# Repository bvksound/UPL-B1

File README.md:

UPL-B1 Low Distortion Generator — Functional Description (Sheets 1–5)

The UPL-B1 is a digitally controlled, ultra-low-distortion sine-wave generator. It operates by forming a precisely tuned analog feedback loop based on two integrators, a loop inverter, a fine-tuning DAC, and an ultra-slow automatic level control system. The resulting sine wave is then routed through a calibrated output attenuator to the LOW DIST output connector.

The block diagram in Sheet 1 shows how the system is organized.
What follows is the working description of each functional block in the signal path.

⸻

1. Digital Control Interface (Data Link)

(Located in sheet 1)

At the heart of the module’s control architecture is the Data Link, which acts as the communication interface between the UPL main processor and all analog functions of the generator. A chain of serial-in/parallel-out registers receives configuration words via the UPL’s internal bus. Once a word is clocked in and latched, each bit becomes a control signal for:
	•	selecting RC networks inside the frequency-defining integrators,
	•	programming the 12-bit DAC used for fine frequency tuning,
	•	configuring the ALC’s track-and-hold behavior,
	•	setting the output level via the IMD attenuator.

In this way, the Data Link provides complete, deterministic configuration of the low-distortion generator through a simple serial interface.

⸻

2. First Loop Element: Integrator 2

(Located in sheet 4)

The oscillator loop begins with Integrator 2, which receives the feedback signal from the loop inverter. This block is a precision analog integrator with a set of relay- and switch-selectable RC networks. These RC combinations determine the coarse frequency range of the oscillator.

Because the transfer function of an integrator introduces a –90° phase shift, this element contributes the first quadrature shift in the loop. The output of this block is labelled SIN. It serves as both a phase-shifted signal for the next integrator and as a key reference for amplitude monitoring in the ALC.

⸻

3. Second Loop Element: Integrator 1, and the Loop Inverter

(Both located in sheet 3)

Integrator 1 — second 90° phase shift

The SIN signal from Integrator 2 is fed into Integrator 1, which is structurally similar—another precision op-amp stage with switchable RC networks.
This second integrator produces the COS signal, shifted by another –90°.
Together, the two integrators establish the total –180° shift required by the oscillator’s feedback loop.

Fine Frequency Tuning (DAC + Summing Amplifier)

A portion of the COS signal is routed into a 12-bit DAC system, whose output feeds a summing amplifier. This mechanism provides continuous fine frequency adjustment within each coarse RC range.
The UPL’s firmware writes a digital tuning word via the Data Link, and the DAC modifies the loop dynamics subtly to achieve precise output frequency control.

Loop Inverter — completes the oscillation path

The Loop Inverter receives signals from the fine-tuning circuit and the integrator chain and produces the required additional –180° phase inversion, closing the total loop phase at 360° (0° net).
The loop inverter also establishes the oscillator’s effective feedback gain, which is later stabilized by the amplitude control system.

The output of the loop inverter is fed back to Integrator 2, completing the analog oscillator core.

⸻

4. Amplitude Regulation: The Automatic Level Control (ALC)

(Located in sheet 5)

A precision sine-wave oscillator will naturally drift or saturate unless its amplitude is regulated. In the UPL-B1, this regulation is handled by the Automatic Level Control (ALC) system.

Amplitude Sampling and Track-and-Hold

A portion of the SIN waveform is extracted and fed into a track-and-hold detector.
This allows the ALC to operate cleanly over the full frequency range of the generator—including very low frequencies—where a conventional detector would otherwise create distortion or instability.

Precision Detection and Error Generation

The sampled waveform is rectified and converted into a DC level proportional to its amplitude.
A summing amplifier compares this value to an internally established reference representing the desired output level.

Slow, Low-Distortion Control Loop

The resulting error signal passes through carefully designed low-frequency filters.
These filters ensure that the ALC’s response is extremely slow—far outside the audio band—so that no gain modulation occurs within the audible range. This is critical for achieving the exceptionally low distortion performance of the UPL-B1.

VCA Gain Element

The filtered control voltage drives a voltage-controlled amplifier (VCA) in the main signal path.
When the amplitude is too low, the VCA’s gain increases; when too high, it decreases.
When equilibrium is reached, the loop gain of the oscillator is exactly unity, resulting in a stable, clean sine of precisely controlled amplitude.

The regulated sine now moves to the final output stage.

⸻

5. Output Level Setting: IMD Attenuator

(Located in sheet 2)

The final block is the IMD Attenuator, responsible for delivering calibrated output levels to the LOW DIST connector.
The attenuator uses relay-selected resistor networks combined with precision buffer amplification. Control bits from the Data Link determine the selected attenuation step.

Unlike the ALC-governed gain element, the IMD attenuator applies fixed, accurate attenuation values that do not interact with the oscillator’s internal amplitude regulation. This ensures:
	•	repeatable, calibration-grade output levels,
	•	reliable IMD and THD measurement conditions,
	•	and isolation of the internal oscillator loop from load-dependent variations.

The output of this attenuator is the module’s LOW DIST signal.

⸻

Complete Signal Flow (at a glance)
	1.	UPL processor configures the module via the Data Link (Sheet 1).
	2.	The signal enters Integrator 2 (Sheet 4) which adds the first –90° phase shift.
	3.	It then enters Integrator 1 (Sheet 3) for another –90° shift, producing COS.
	4.	The signal passes through the fine-tuning DAC and the Loop Inverter (Sheet 3), closing the loop.
	5.	The resulting oscillation is amplitude-stabilized by the ALC system (Sheet 5).
	6.	The regulated sine enters the IMD Attenuator (Sheet 2).
	7.	The final output appears as LOW DIST, ready for measurement applications.

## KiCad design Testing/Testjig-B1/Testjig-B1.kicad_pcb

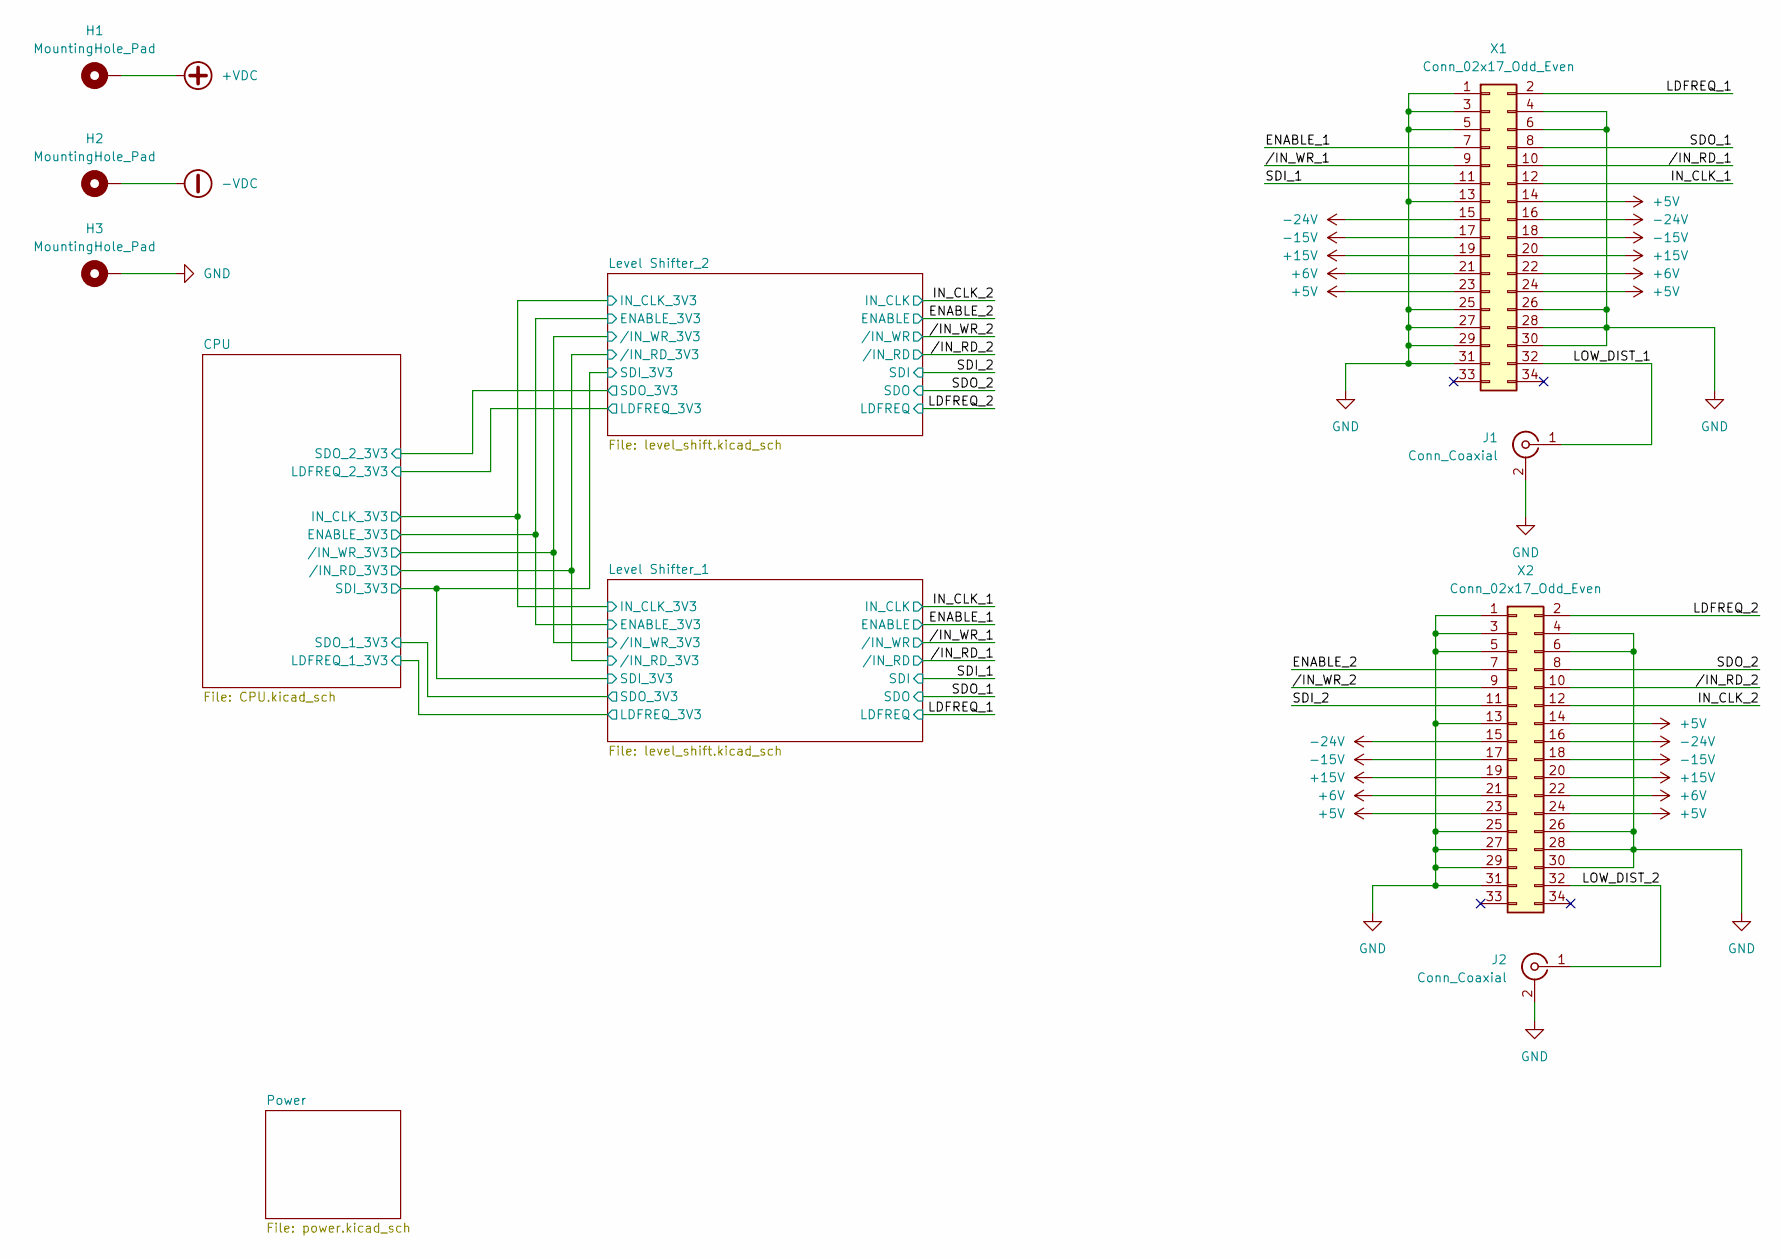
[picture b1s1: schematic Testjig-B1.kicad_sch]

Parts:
H1, H2, H3: MountingHole_Pad; MountingHole_6.4mm_M6_DIN965_Pad
J1, J2: Conn_Coaxial; BNC_Amphenol_031-5539_Vertical
X1, X2: Conn_02x17_Odd_Even; IDC-Header_2x17_P2.54mm_Vertical

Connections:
+5V: X1.14, X1.23, X1.24, X2.14, X2.23, X2.24; also elsewhere on the board
+6V: X1.21, X1.22, X2.21, X2.22; also elsewhere on the board
+15V: X1.19, X1.20, X2.19, X2.20; also elsewhere on the board
+VDC: H1.1 (1_1); also elsewhere on the board
-15V: X1.17, X1.18, X2.17, X2.18; also elsewhere on the board
-24V: X1.15, X1.16, X2.15, X2.16; also elsewhere on the board
-VDC: H2.1 (1_1); also elsewhere on the board
/ENABLE_1: X1.7; also elsewhere on the board
/ENABLE_2: X2.7; also elsewhere on the board
/IN_CLK_1: X1.12; also elsewhere on the board
/IN_CLK_2: X2.12; also elsewhere on the board
/LDFREQ_1: X1.2; also elsewhere on the board
/LDFREQ_2: X2.2; also elsewhere on the board
/LOW_DIST_1: J1.1 (In), X1.32
/LOW_DIST_2: J2.1 (In), X2.32
/SDI_1: X1.11; also elsewhere on the board
/SDI_2: X2.11; also elsewhere on the board
/SDO_1: X1.8; also elsewhere on the board
/SDO_2: X2.8; also elsewhere on the board
//IN_RD_1: X1.10; also elsewhere on the board
//IN_RD_2: X2.10; also elsewhere on the board
//IN_WR_1: X1.9; also elsewhere on the board
//IN_WR_2: X2.9; also elsewhere on the board
GND: H3.1 (1_1), J1.2 (Ext), J2.2 (Ext), X1.1, X1.3, X1.4, X1.5, X1.6, X1.13, X1.25, X1.26, X1.27, X1.28, X1.29, X1.30, X1.31, X2.1, X2.3, X2.4, X2.5, X2.6, X2.13, X2.25, X2.26, X2.27, X2.28, X2.29, X2.30, X2.31; also elsewhere on the board

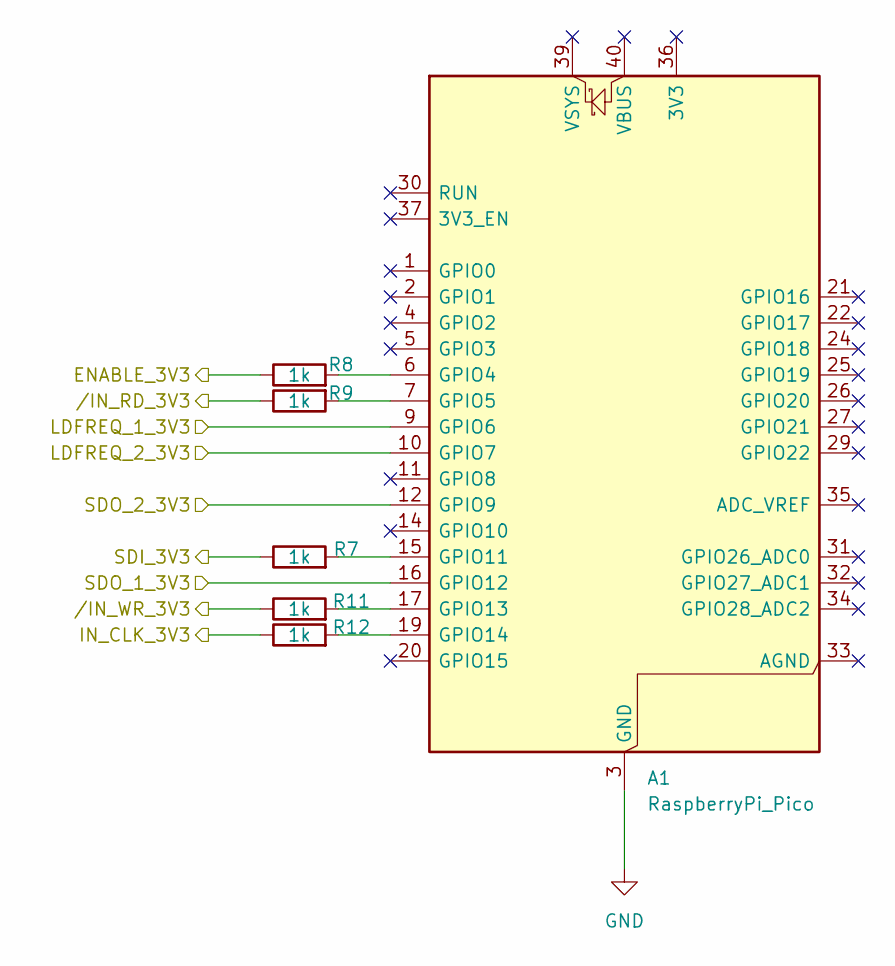
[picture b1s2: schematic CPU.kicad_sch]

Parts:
A1: RaspberryPi_Pico; RaspberryPi_Pico_Common_Unspecified
R7, R8, R9, R11, R12: 1k; R_0805_2012Metric

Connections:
/CPU/ENABLE_3V3: R8.1; also elsewhere on the board
/CPU/IN_CLK_3V3: R12.1; also elsewhere on the board
/CPU/LDFREQ_1_3V3: A1.9 (GPIO6); also elsewhere on the board
/CPU/LDFREQ_2_3V3: A1.10 (GPIO7); also elsewhere on the board
/CPU/SDI_3V3: R7.1; also elsewhere on the board
/CPU/SDO_1_3V3: A1.16 (GPIO12); also elsewhere on the board
/CPU/SDO_2_3V3: A1.12 (GPIO9); also elsewhere on the board
/CPU//IN_RD_3V3: R9.1; also elsewhere on the board
/CPU//IN_WR_3V3: R11.1; also elsewhere on the board
GND: A1.3 (GND), A1.8 (GND), A1.13 (GND), A1.18 (GND), A1.23 (GND), A1.28 (GND), A1.38 (GND); also elsewhere on the board
unnamed: A1.6 (GPIO4), R8.2
unnamed: A1.7 (GPIO5), R9.2
unnamed: A1.15 (GPIO11), R7.2
unnamed: A1.17 (GPIO13), R11.2
unnamed: A1.19 (GPIO14), R12.2

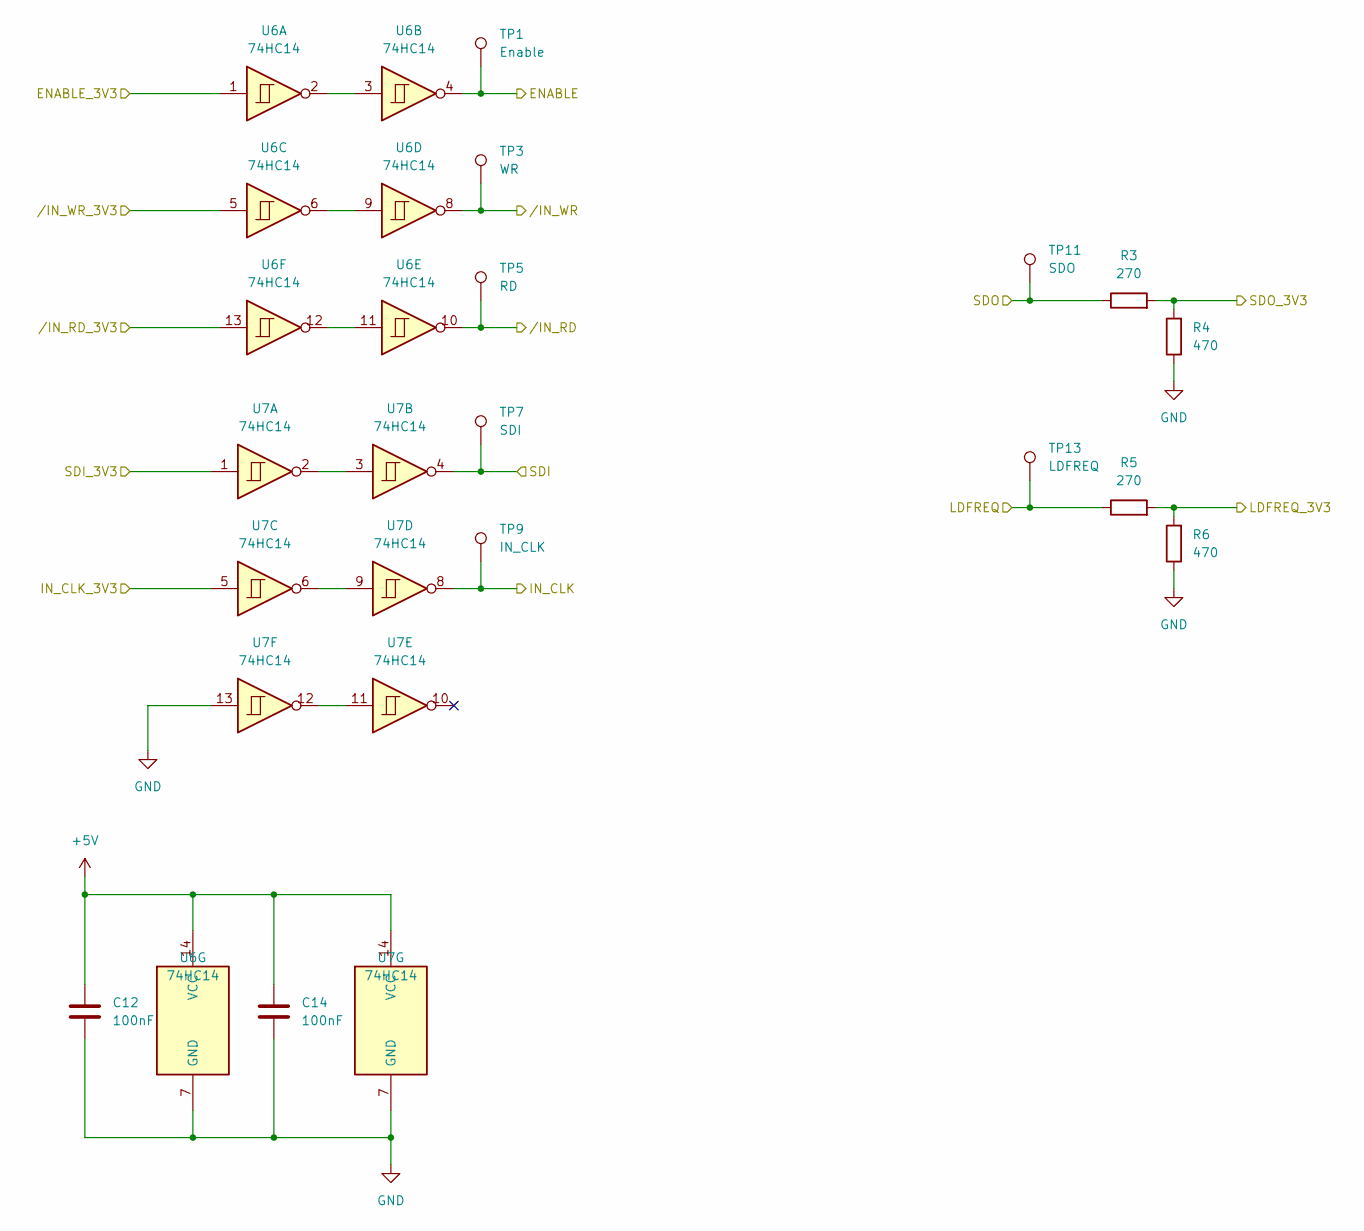
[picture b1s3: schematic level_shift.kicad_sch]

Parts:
C12, C14: 100nF; C_0805_2012Metric_Pad1.18x1.45mm_HandSolder
R3, R5: 270; R_0805_2012Metric
R4, R6: 470; R_0805_2012Metric
TP1: Enable; TestPoint_Loop_D2.60mm_Drill1.4mm_Beaded
TP3: WR; TestPoint_Loop_D2.60mm_Drill1.4mm_Beaded
TP5: RD; TestPoint_Loop_D2.60mm_Drill1.4mm_Beaded
TP7: SDI; TestPoint_Loop_D2.60mm_Drill1.4mm_Beaded
TP9: IN_CLK; TestPoint_Loop_D2.60mm_Drill1.4mm_Beaded
TP11: SDO; TestPoint_Loop_D2.60mm_Drill1.4mm_Beaded
TP13: LDFREQ; TestPoint_Loop_D2.60mm_Drill1.4mm_Beaded
U6, U7: 74HC14; SOIC-14_3.9x8.7mm_P1.27mm

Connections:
+5V: C12.1, C14.1, U6.14 (VCC), U7.14 (VCC); also elsewhere on the board
/CPU/ENABLE_3V3: U6.1; also elsewhere on the board
/CPU/IN_CLK_3V3: U7.5; also elsewhere on the board
/CPU/LDFREQ_1_3V3: R5.2, R6.2; also elsewhere on the board
/CPU/SDI_3V3: U7.1; also elsewhere on the board
/CPU/SDO_1_3V3: R3.2, R4.2; also elsewhere on the board
/CPU//IN_RD_3V3: U6.13; also elsewhere on the board
/CPU//IN_WR_3V3: U6.5; also elsewhere on the board
/ENABLE_1: TP1.1 (1_1), U6.4; also elsewhere on the board
/IN_CLK_1: TP9.1 (1_1), U7.8; also elsewhere on the board
/LDFREQ_1: R5.1, TP13.1 (1_1); also elsewhere on the board
/SDI_1: TP7.1 (1_1), U7.4; also elsewhere on the board
/SDO_1: R3.1, TP11.1 (1_1); also elsewhere on the board
//IN_RD_1: TP5.1 (1_1), U6.10; also elsewhere on the board
//IN_WR_1: TP3.1 (1_1), U6.8; also elsewhere on the board
GND: C12.2, C14.2, R4.1, R6.1, U6.7 (GND), U7.7 (GND), U7.13; also elsewhere on the board
unnamed: U6.2, U6.3
unnamed: U6.6, U6.9
unnamed: U6.11, U6.12
unnamed: U7.2, U7.3
unnamed: U7.6, U7.9
unnamed: U7.11, U7.12

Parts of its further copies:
C13, C15: 100nF; C_0805_2012Metric_Pad1.18x1.45mm_HandSolder
R13, R14: 270; R_0805_2012Metric
R15, R16: 470; R_0805_2012Metric
TP2: Enable; TestPoint_Loop_D2.60mm_Drill1.4mm_Beaded
TP4: WR; TestPoint_Loop_D2.60mm_Drill1.4mm_Beaded
TP6: RD; TestPoint_Loop_D2.60mm_Drill1.4mm_Beaded
TP8: SDI; TestPoint_Loop_D2.60mm_Drill1.4mm_Beaded
TP10: IN_CLK; TestPoint_Loop_D2.60mm_Drill1.4mm_Beaded
TP12: SDO; TestPoint_Loop_D2.60mm_Drill1.4mm_Beaded
TP14: LDFREQ; TestPoint_Loop_D2.60mm_Drill1.4mm_Beaded
U8, U9: 74HC14; SOIC-14_3.9x8.7mm_P1.27mm

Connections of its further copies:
+5V: C13.1, C15.1, U8.14 (VCC), U9.14 (VCC); also elsewhere on the board
/CPU/ENABLE_3V3: U8.1; also elsewhere on the board
/CPU/IN_CLK_3V3: U9.5; also elsewhere on the board
/CPU/LDFREQ_2_3V3: R14.2, R16.2; also elsewhere on the board
/CPU/SDI_3V3: U9.1; also elsewhere on the board
/CPU/SDO_2_3V3: R13.2, R15.2; also elsewhere on the board
/CPU//IN_RD_3V3: U8.13; also elsewhere on the board
/CPU//IN_WR_3V3: U8.5; also elsewhere on the board
/ENABLE_2: TP2.1 (1_1), U8.4; also elsewhere on the board
/IN_CLK_2: TP10.1 (1_1), U9.8; also elsewhere on the board
/LDFREQ_2: R14.1, TP14.1 (1_1); also elsewhere on the board
/SDI_2: TP8.1 (1_1), U9.4; also elsewhere on the board
/SDO_2: R13.1, TP12.1 (1_1); also elsewhere on the board
//IN_RD_2: TP6.1 (1_1), U8.10; also elsewhere on the board
//IN_WR_2: TP4.1 (1_1), U8.8; also elsewhere on the board
GND: C13.2, C15.2, R15.1, R16.1, U8.7 (GND), U9.7 (GND), U9.13; also elsewhere on the board
unnamed: U8.2, U8.3
unnamed: U8.6, U8.9
unnamed: U8.11, U8.12
unnamed: U9.2, U9.3
unnamed: U9.6, U9.9
unnamed: U9.11, U9.12

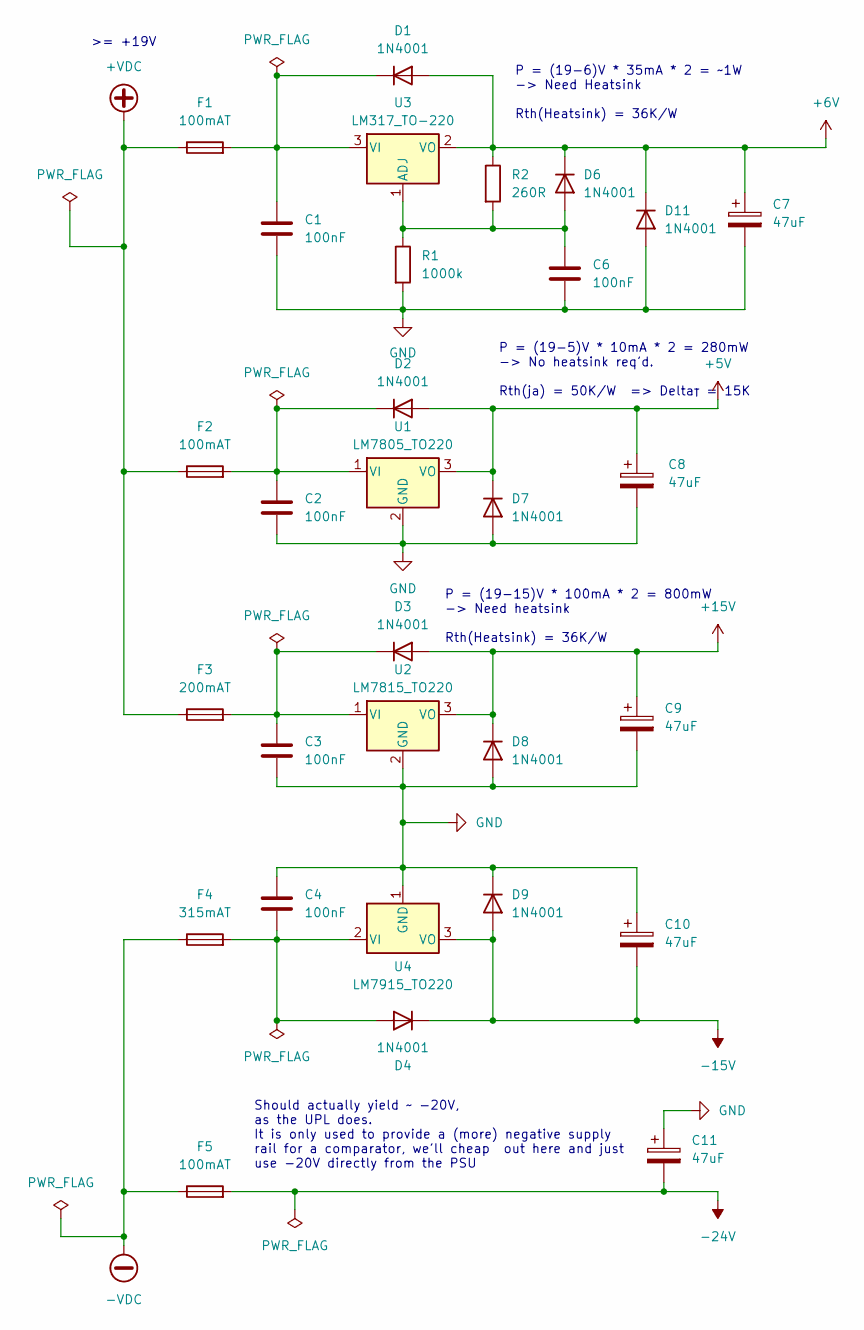
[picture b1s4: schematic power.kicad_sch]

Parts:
C1, C2, C3, C4, C6: 100nF; C_0805_2012Metric_Pad1.18x1.45mm_HandSolder
C7, C8, C9, C10, C11: 47uF; CP_Radial_D6.3mm_P2.50mm
D1, D2, D3, D4, D6, D7, D8, D9, D11: 1N4001; D_DO-41_SOD81_P10.16mm_Horizontal
F1, F2, F5: 100mAT; Fuseholder_Cylinder-5x20mm_Schurter_0031_8201_Horizontal_Op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
F3: 200mAT; Fuseholder_Cylinder-5x20mm_Schurter_0031_8201_Horizontal_Op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
F4: 315mAT; Fuseholder_Cylinder-5x20mm_Schurter_0031_8201_Horizontal_Op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
R1: 1000k; R_0805_2012Metric
R2: 260R; R_0805_2012Metric
U1: LM7805_TO220; TO-220-3_Vertical
U2: LM7815_TO220; TO-220-3_Vertical
U3: LM317_TO-220; TO-220-3_Vertical
U4: LM7915_TO220; TO-220-3_Vertical

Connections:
+5V: C8.1, D2.2 (A), D7.1 (K), U1.3 (VO); also elsewhere on the board
+6V: C7.1, D1.2 (A), D6.1 (K), D11.1 (K), R2.1, U3.2 (VO); also elsewhere on the board
+15V: C9.1, D3.2 (A), D8.1 (K), U2.3 (VO); also elsewhere on the board
+VDC: F1.1, F2.1, F3.1; also elsewhere on the board
-15V: C10.2, D4.1 (K), D9.2 (A), U4.3 (VO); also elsewhere on the board
-24V: C11.2, F5.2; also elsewhere on the board
-VDC: F4.1, F5.1; also elsewhere on the board
GND: C1.2, C2.2, C3.2, C4.1, C6.2, C7.2, C8.2, C9.2, C10.1, C11.1, D7.2 (A), D8.2 (A), D9.1 (K), D11.2 (A), R1.2, U1.2 (GND), U2.2 (GND), U4.1 (GND); also elsewhere on the board
unnamed: C1.1, D1.1 (K), F1.2, U3.3 (VI)
unnamed: C2.1, D2.1 (K), F2.2, U1.1 (VI)
unnamed: C3.1, D3.1 (K), F3.2, U2.1 (VI)
unnamed: C4.2, D4.2 (A), F4.2, U4.2 (VI)
unnamed: C6.1, D6.2 (A), R1.1, R2.2, U3.1 (ADJ)

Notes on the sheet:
>= +19V
P = (19-15)V * 100mA * 2 = 800mW -> Need heatsink Rth(Heatsink) = 36K/W
Should actually yield ~ -20V, as the UPL does. It is only used to provide a (more) negative supply rail for a comparator, we'll cheap out here and just use -20V directly from the PSU
P = (19-6)V * 35mA * 2 = ~1W -> Need Heatsink Rth(Heatsink) = 36K/W
P = (19-5)V * 10mA * 2 = 280mW -> No heatsink req'd. Rth(ja) = 50K/W => Delta_{T} = 15K

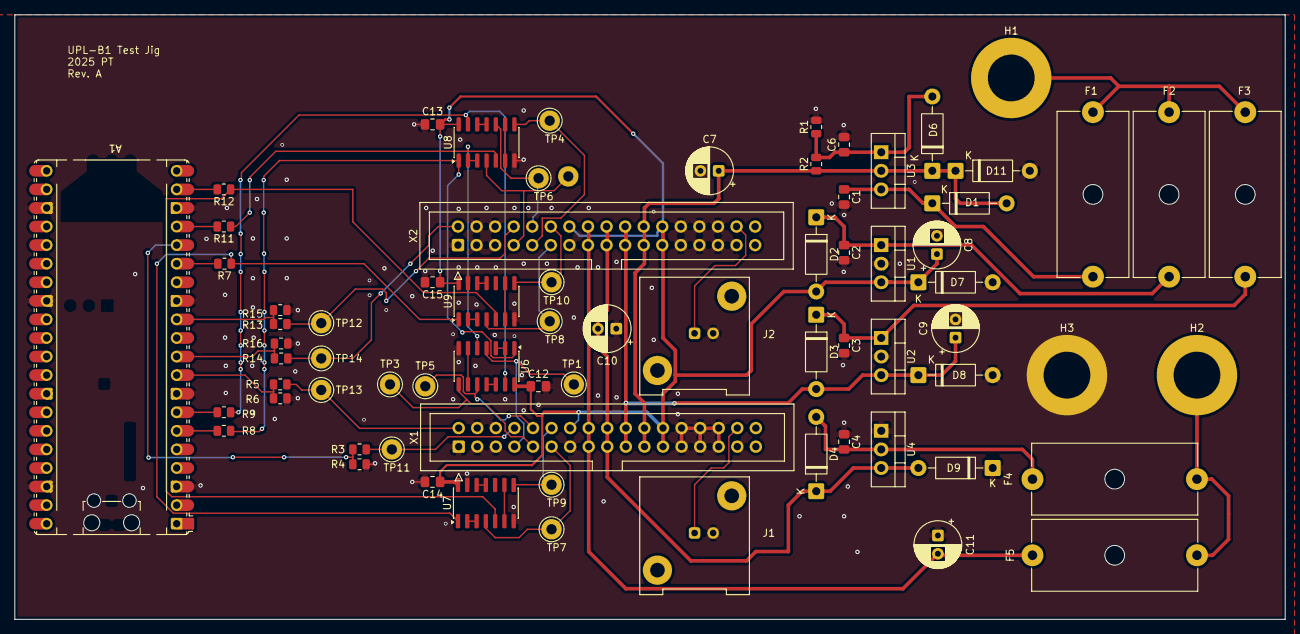
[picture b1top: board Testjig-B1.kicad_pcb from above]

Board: 2 copper layers, 173.7 x 82.7 mm, 73 parts (1 on the bottom side), 55 nets.

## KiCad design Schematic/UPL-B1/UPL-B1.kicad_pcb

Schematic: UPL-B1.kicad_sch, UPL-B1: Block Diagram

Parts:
X1: 5102159-8; CONN_5103311-7_TYC; Mouser Part Number 571-5102159-8
X3, X4: Conn_01x06_Pin; PinHeader_1x06_P2.54mm_Vertical

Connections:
+5V: X1.23, X1.24, X4.1; also elsewhere on the board
+6V: X1.21, X1.22, X4.5
+15V: X1.19, X1.20, X4.2; also elsewhere on the board
-5V: X1.14
-15V: X1.17, X1.18, X4.3; also elsewhere on the board
-24V: X1.15, X1.16, X4.4; also elsewhere on the board
/CLK: X3.4; also elsewhere on the board
/ENABLE: X1.7, X4.6; also elsewhere on the board
/IN_CLK: X1.12; also elsewhere on the board
/LDFREQ: X1.2
/LOW_DIST: X1.34; also elsewhere on the board
/SDI: X1.11, X3.5; also elsewhere on the board
/SDO: X1.8, X3.6; also elsewhere on the board
/WR: X3.1; also elsewhere on the board
//IN_RD: X1.10; also elsewhere on the board
//IN_WR: X1.9; also elsewhere on the board
/~RD: X3.3; also elsewhere on the board
/~WR: X3.2; also elsewhere on the board
GNDD: X1.1, X1.3, X1.4, X1.5, X1.6, X1.13, X1.25, X1.26, X1.27, X1.28, X1.29, X1.30, X1.31, X1.32, X1.33; also elsewhere on the board

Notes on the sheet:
2/3/4/5
T & H (Track & Hold == Sample & Hold) CONTROL
SUMMIERVERSTÄRKER
D31
-6V2
FREQ TUNE
IMD ATTEN
INTEGRATOR 1
D22,N20
D22
D32, N35
12bit
REGLER STABILIZER
D51 N56
N52
D32
SHEET
V500
N51
Integrator 2
V505..V508
V504 C504 N53
D50
COS
N401
X1A 16
N54 V512
SUMMIERVERSTÄRKER SUMMING AMPLIFIER
10Hz ... 110kHz
D23
2/3/4
V510 C551 N55
D30
SUMMING AMPLIFIFER
~ 2V7_{EFF}
V=0..-20dB
+ -
N301
D21
LOOP INVERTER

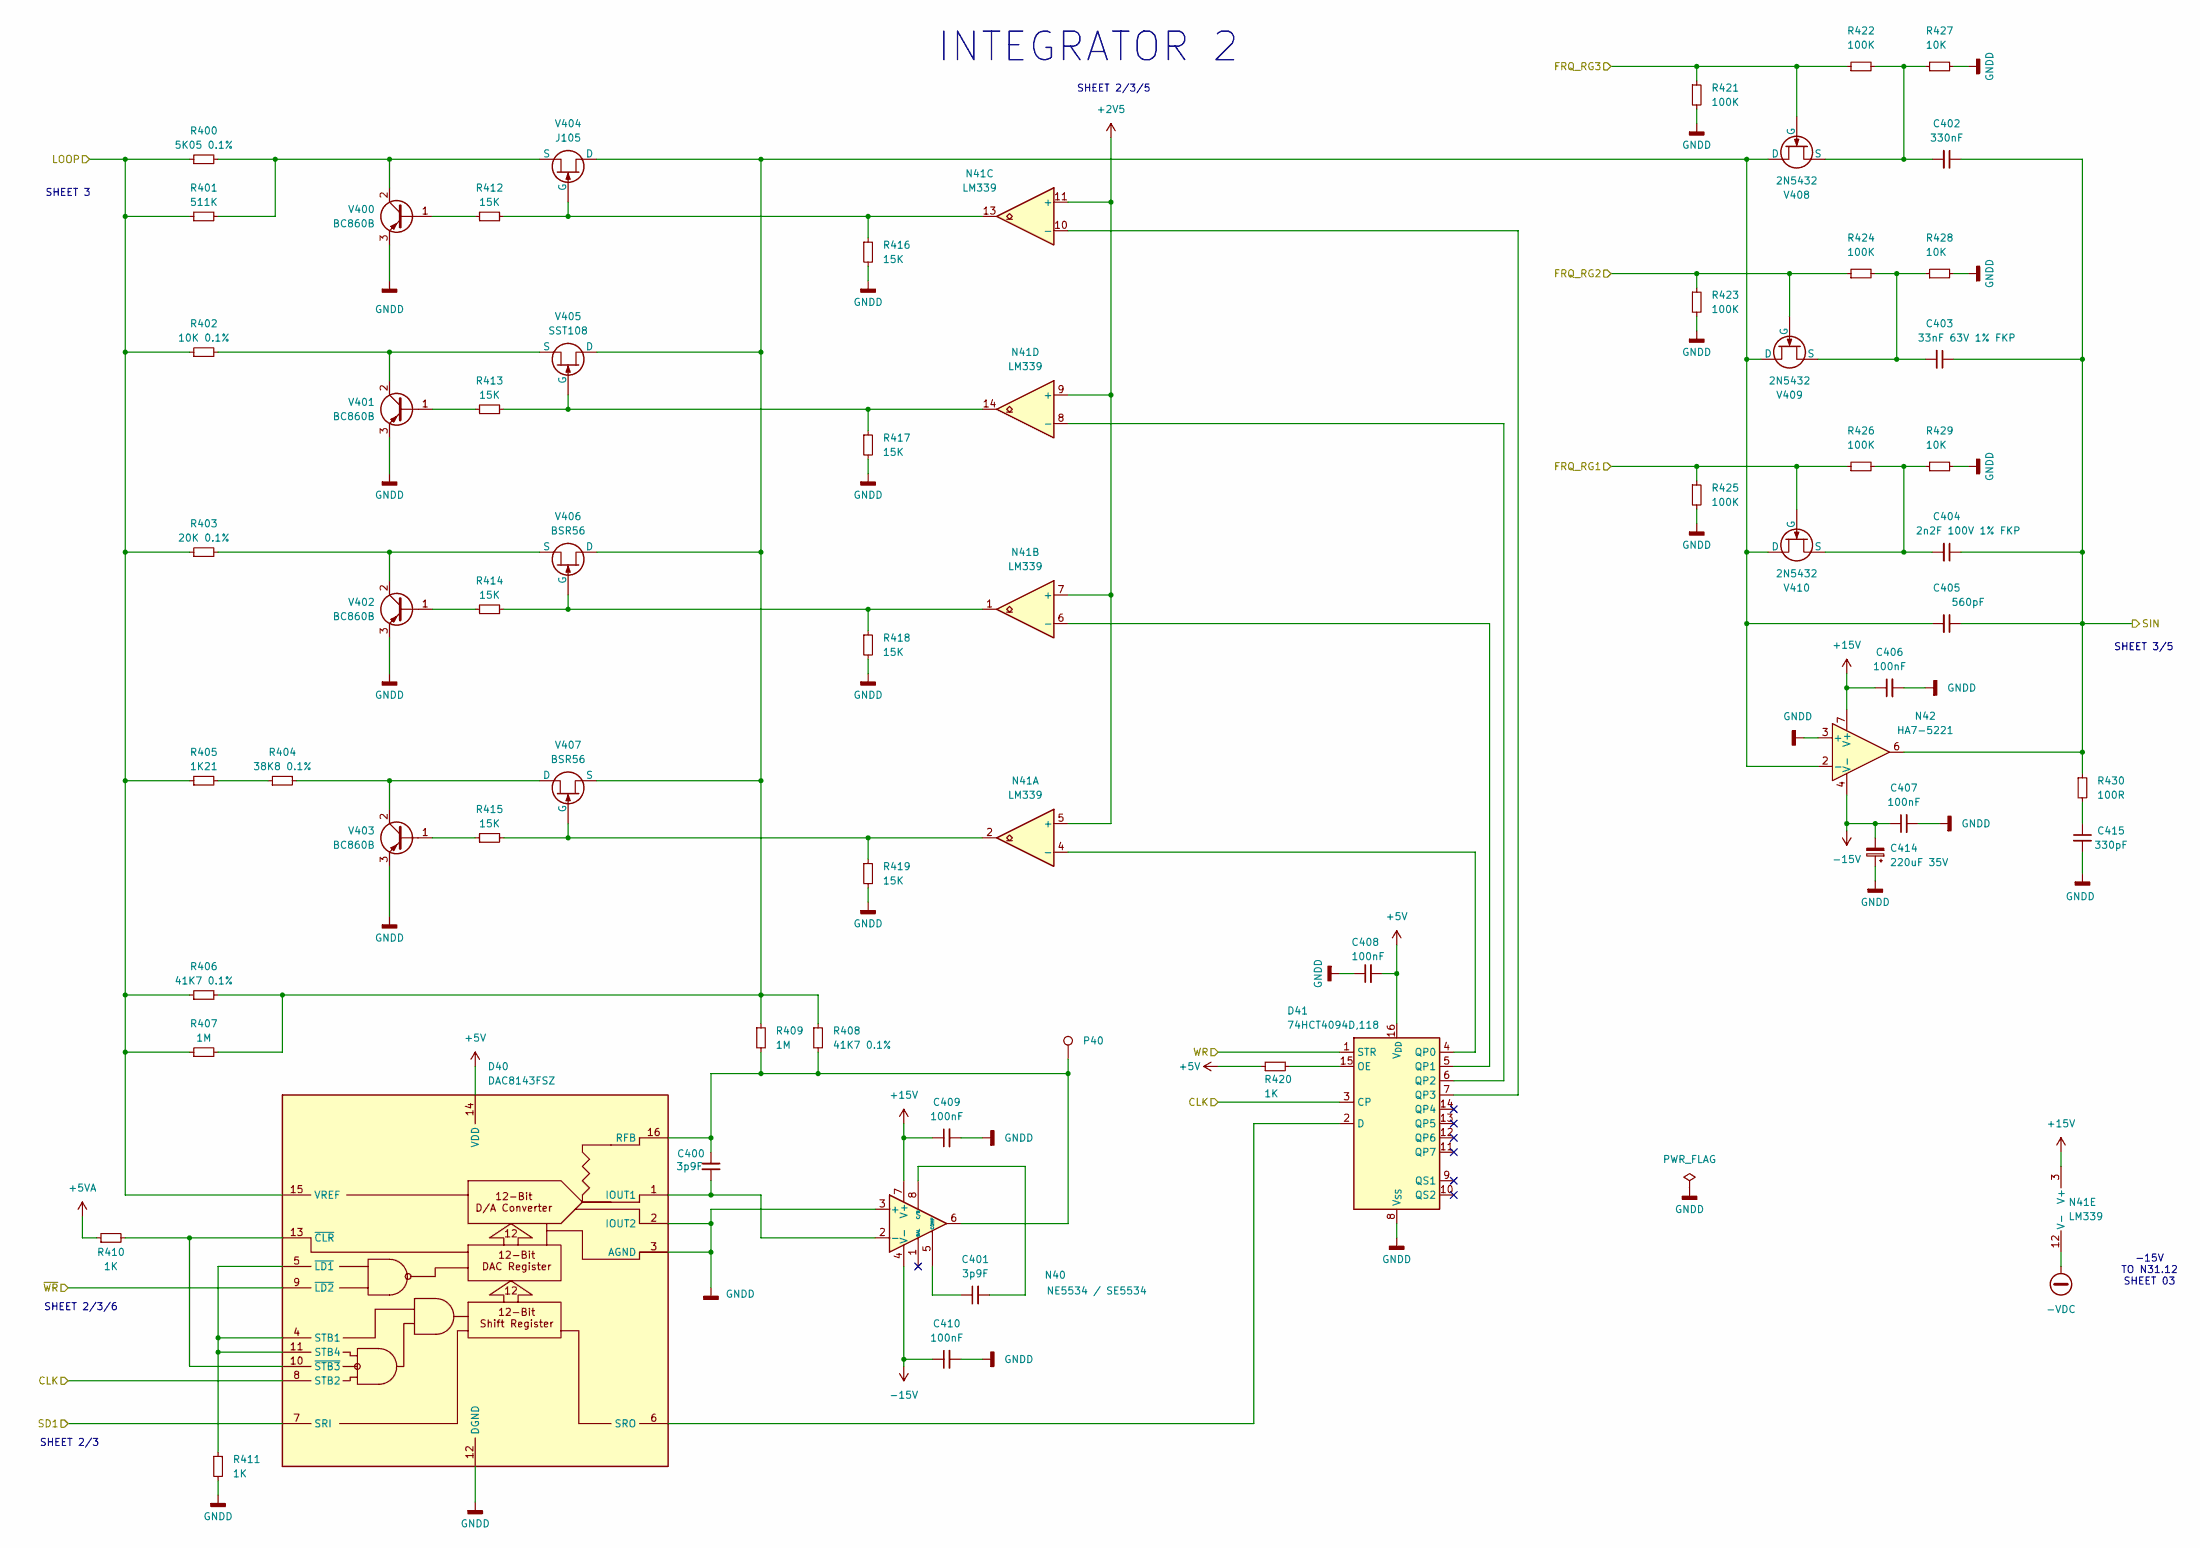
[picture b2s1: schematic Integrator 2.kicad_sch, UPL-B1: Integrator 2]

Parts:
C400, C401: 3p9F; C_1206_3216Metric_Pad1.33x1.80mm_HandSolder
C402: 330nF; C_Axial_L17.0mm_D7.0mm_P25.00mm_Horizontal
C403: 33nF 63V 1% FKP
C404: 2n2F 100V 1% FKP
C405: 560pF; C_1206_3216Metric_Pad1.33x1.80mm_HandSolder
C406, C407, C408, C409, C410: 100nF; C_1206_3216Metric_Pad1.33x1.80mm_HandSolder
C414: 220uF 35V; C_Radial_D10.0mm_H12.5mm_P5.00mm
C415: 330pF; C_1206_3216Metric_Pad1.33x1.80mm_HandSolder
D40: DAC8143FSZ; SOIC-16W_7.5x10.3mm_P1.27mm; Manufacturer_Part_Number DAC8143FSZ
D41: 74HCT4094D,118; SOIC-16_3.9x9.9mm_P1.27mm; Mouser Part Number 771-74HCT4094D-T
N40: NE5534 / SE5534; SOIC-8_3.9x4.9mm_P1.27mm
N41: LM339; SOIC-14_3.9x8.7mm_P1.27mm
N42: HA7-5221; MSOP-8_3x3mm_P0.65mm
P40: TestPoint; PinHeader_1x01_P1.00mm_Vertical
R400: 5K05 0.1%; R_Axial_DIN0204_L3.6mm_D1.6mm_P7.62mm_Horizontal
R401: 511K; R_1206_3216Metric_Pad1.30x1.75mm_HandSolder
R402: 10K 0.1%; R_Axial_DIN0204_L3.6mm_D1.6mm_P7.62mm_Horizontal
R403: 20K 0.1%; R_Axial_DIN0204_L3.6mm_D1.6mm_P7.62mm_Horizontal
R404: 38K8 0.1%; R_Axial_DIN0204_L3.6mm_D1.6mm_P7.62mm_Horizontal
R405: 1K21; R_1206_3216Metric_Pad1.30x1.75mm_HandSolder
R406, R408: 41K7 0.1%; R_Axial_DIN0204_L3.6mm_D1.6mm_P7.62mm_Horizontal
R407, R409: 1M; R_1206_3216Metric_Pad1.30x1.75mm_HandSolder
R410, R411, R420: 1K; R_1206_3216Metric_Pad1.30x1.75mm_HandSolder
R412, R413, R414, R415, R416, R417, R418, R419: 15K; R_1206_3216Metric_Pad1.30x1.75mm_HandSolder
R421, R422, R423, R424, R425, R426: 100K; R_1206_3216Metric_Pad1.30x1.75mm_HandSolder
R427, R428, R429: 10K; R_1206_3216Metric_Pad1.30x1.75mm_HandSolder
R430: 100R; R_1206_3216Metric_Pad1.30x1.75mm_HandSolder
V400, V401, V402, V403: BC860B; SOT-23
V404: J105; TO-92L_Inline
V405: SST108; SOT-23
V406, V407: BSR56; SOT-23
V408, V409, V410: 2N5432; TO-52-3

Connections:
+2V5: N41.5 (+), N41.7 (+), N41.9 (+), N41.11 (+); also elsewhere on the board
+5V: C408.2, D40.14 (VDD), D41.16 (V_{DD}), R420.1; also elsewhere on the board
+5VA: R410.1; also elsewhere on the board
+15V: C406.1, C409.1, N40.7 (V+), N41.3 (V+), N42.7 (V+); also elsewhere on the board
-15V: C407.1, C410.1, C414.2, N40.4 (V-), N42.4 (V-); also elsewhere on the board
-VDC: N41.12 (V-); also elsewhere on the board
/CLK: D40.8 (STB2), D41.3 (CP); also elsewhere on the board
/Integrator 1 & Loop Inverter/FRQ_RG1: R425.1, R426.1, V410.2 (G); also elsewhere on the board
/Integrator 1 & Loop Inverter/FRQ_RG2: R423.1, R424.1, V409.2 (G); also elsewhere on the board
/Integrator 1 & Loop Inverter/FRQ_RG3: R421.1, R422.1, V408.2 (G); also elsewhere on the board
/LOOP: D40.15 (VREF), R400.1, R401.1, R402.1, R403.1, R405.1, R406.1, R407.1; also elsewhere on the board
/SD1: D40.7 (SRI); also elsewhere on the board
/WR: D41.1 (STR); also elsewhere on the board
/~WR: D40.9 (~LD2); also elsewhere on the board
GNDD: C406.2, C407.2, C408.1, C409.2, C410.2, C414.1, C415.2, D40.2 (IOUT2), D40.3 (AGND), D40.12 (DGND), D41.8 (V_{SS}), N40.3 (+), N42.3 (+), R411.2, R416.2, R417.2, R418.2, R419.2, R421.2, R423.2, R425.2, R427.2, R428.2, R429.2, V400.3 (E), V401.3 (E), V402.3 (E), V403.3 (E); also elsewhere on the board
unnamed: C415.1, R430.2
unnamed: C400.1, D40.1 (IOUT1), N40.2 (-)
unnamed: C400.2, D40.16 (RFB), N40.6, P40.1, R408.2, R409.2
unnamed: D40.6 (SRO), D41.2 (D)
unnamed: D40.4 (STB1), D40.5 (~LD1), D40.11 (STB4), R411.1
unnamed: D40.10 (~STB3), D40.13 (~CLR), R410.2
unnamed: D41.15 (OE), R420.2
unnamed: D41.4 (QP0), N41.4 (-)
unnamed: D41.5 (QP1), N41.6 (-)
unnamed: D41.6 (QP2), N41.8 (-)
unnamed: D41.7 (QP3), N41.10 (-)
unnamed: C401.1, N40.5 (COMP)
unnamed: C401.2, N40.8 (C/B)
unnamed: C405.2, N42.2 (-), R406.2, R407.2, R408.1, R409.1, V404.1 (D), V405.1 (D), V406.1 (D), V407.3 (S), V408.1 (D), V409.1 (D), V410.1 (D)
unnamed: R404.1, R405.2
unnamed: R412.1, V400.1 (B)
unnamed: R400.2, R401.2, V400.2 (C), V404.3 (S)
unnamed: R413.1, V401.1 (B)
unnamed: R402.2, V401.2 (C), V405.3 (S)
unnamed: R414.1, V402.1 (B)
unnamed: R403.2, V402.2 (C), V406.3 (S)
unnamed: R415.1, V403.1 (B)
unnamed: R404.2, V403.2 (C), V407.1 (D)
unnamed: N41.13, R412.2, R416.1, V404.2 (G)
unnamed: N41.14, R413.2, R417.1, V405.2 (G)
unnamed: N41.1, R414.2, R418.1, V406.2 (G)
unnamed: N41.2, R415.2, R419.1, V407.2 (G)
unnamed: C402.2, R422.2, R427.1, V408.3 (S)
unnamed: C403.2, R424.2, R428.1, V409.3 (S)
unnamed: C404.2, R426.2, R429.1, V410.3 (S)
SIN: C402.1, C403.1, C404.1, C405.1, N42.6, R430.1; also elsewhere on the board

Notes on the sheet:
-15V TO N31.12 SHEET 03
INTEGRATOR 2
SHEET 2/3/5
SHEET 2/3/6
SHEET 3/5
SHEET 2/3
SHEET 3
